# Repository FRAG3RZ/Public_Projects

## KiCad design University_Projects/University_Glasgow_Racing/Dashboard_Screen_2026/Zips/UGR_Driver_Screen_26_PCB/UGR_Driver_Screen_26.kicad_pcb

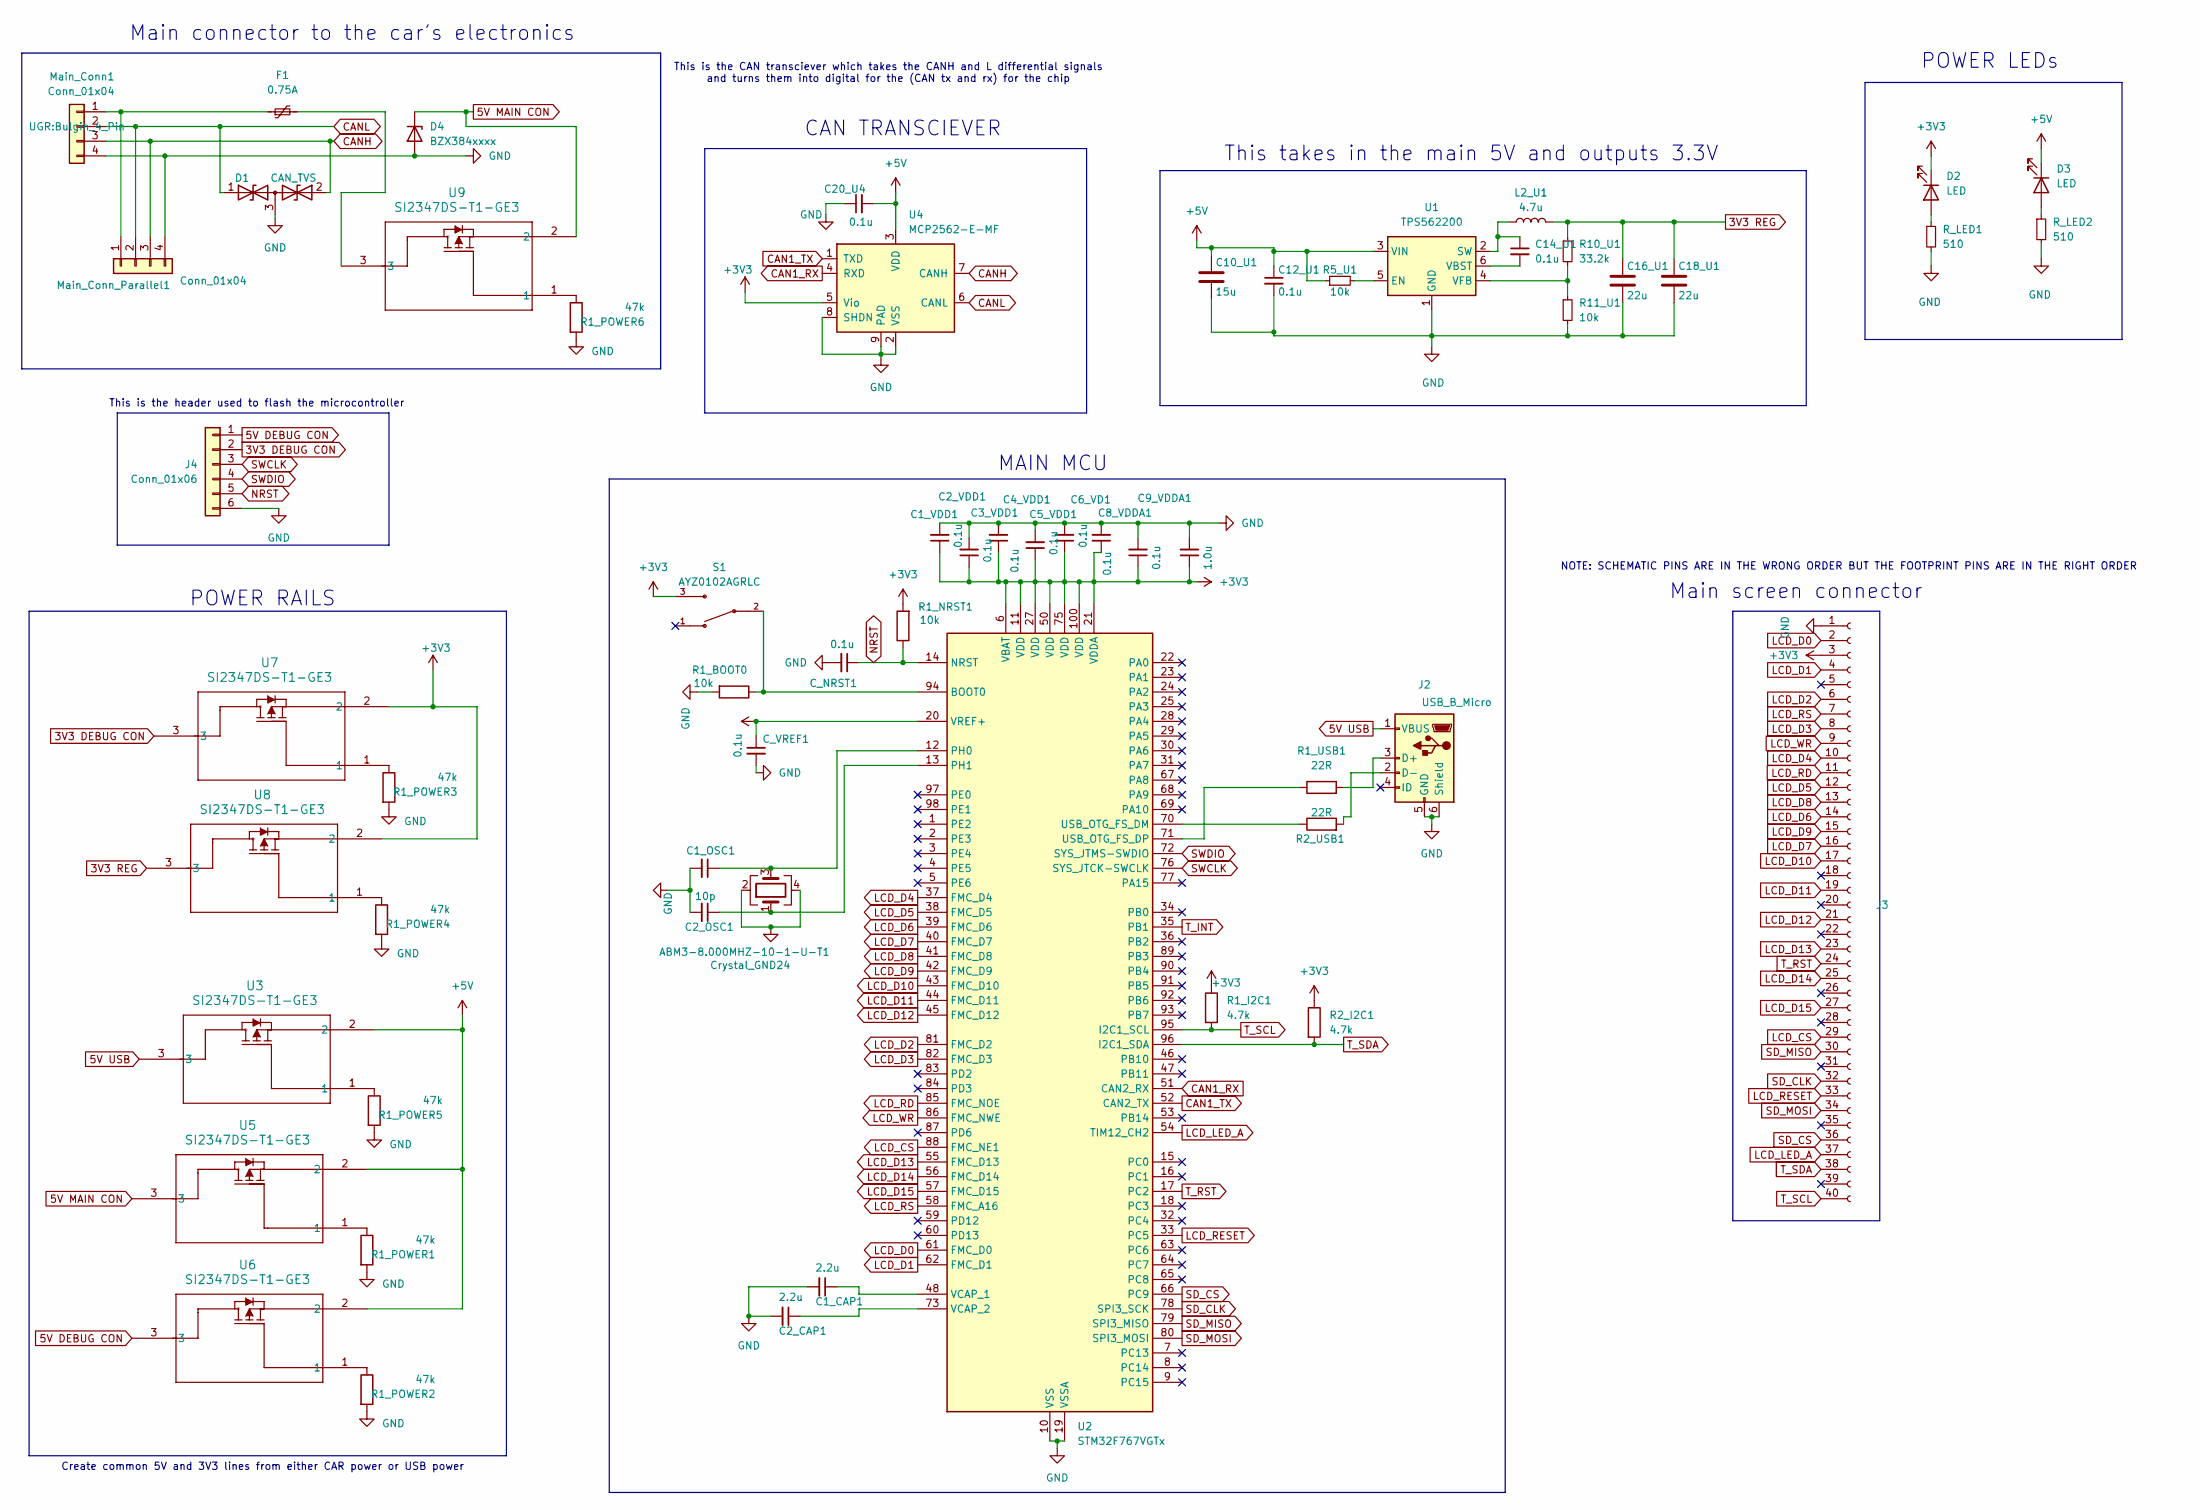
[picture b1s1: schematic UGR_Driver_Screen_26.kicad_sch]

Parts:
ABM3-8.000MHZ-10-1-U-T1: Crystal_GND24; Crystal_SMD_Abracon_ABM3B-4Pin_5.0x3.2mm
C1_CAP1, C2_CAP1: 2.2u; C_0603_1608Metric_Pad1.08x0.95mm_HandSolder
C1_OSC1, C2_OSC1: 10p; C_0603_1608Metric_Pad1.08x0.95mm_HandSolder
C1_VDD1, C2_VDD1, C3_VDD1, C4_VDD1, C5_VDD1, C6_VD1, C8_VDDA1, C12_U1, C14_U1, C20_U4: 0.1u; C_0603_1608Metric_Pad1.08x0.95mm_HandSolder
C9_VDDA1: 1.0u; C_0603_1608Metric_Pad1.08x0.95mm_HandSolder
C10_U1: 15u; C_1210_3225Metric_Pad1.33x2.70mm_HandSolder
C16_U1, C18_U1: 22u; C_1210_3225Metric_Pad1.33x2.70mm_HandSolder
C_NRST1: 0.1u; C_0603_1608Metric_Pad1.08x0.95mm_HandSolder
C_VREF1: 0.1u; C_0603_1608Metric_Pad1.08x0.95mm_HandSolder
D1: CAN_TVS; SOT-23; Manufacturer Part No. SZNUP2105L
D2, D3: LED; PinHeader_1x02_P2.54mm_Vertical
D4: BZX384xxxx; D_SOD-323
F1: 0.75A; Fuse_1812_4532Metric_Pad1.30x3.40mm_HandSolder; Manufacturer Part No. 1206L075/16WR
J2: USB_B_Micro; USB_Micro-B_Wuerth_629105150521
J3: Conn_02x20_Socket; PinSocket_2x20_P2.54mm_Vertical
J4: Conn_01x06; PinHeader_1x06_P2.54mm_Vertical
L2_U1: 4.7u; L_1206_3216Metric_Pad1.42x1.75mm_HandSolder
Main_Conn1: Conn_01x04; Bulgin_4_Pin
Main_Conn_Parallel1: Conn_01x04; PinHeader_1x04_P2.54mm_Vertical
R1_BOOT0, R1_NRST1, R5_U1, R11_U1: 10k; R_0603_1608Metric_Pad0.98x0.95mm_HandSolder
R1_I2C1, R2_I2C1: 4.7k; R_0603_1608Metric_Pad0.98x0.95mm_HandSolder
R1_POWER1, R1_POWER2, R1_POWER3, R1_POWER4, R1_POWER5, R1_POWER6: 47k; R_0603_1608Metric_Pad0.98x0.95mm_HandSolder
R1_USB1, R2_USB1: 22R; R_0603_1608Metric_Pad0.98x0.95mm_HandSolder
R10_U1: 33.2k; R_0603_1608Metric_Pad0.98x0.95mm_HandSolder
R_LED1, R_LED2: 510; R_0603_1608Metric_Pad0.98x0.95mm_HandSolder
S1: AYZ0102AGRLC; SW_AYZ0102AGRLC
U1: TPS562200; SOT-23-6
U2: STM32F767VGTx; LQFP-100_14x14mm_P0.5mm
U3, U5, U6, U7, U8, U9: SI2347DS-T1-GE3; SOT_7DS-T1-GE3_VIS
U4: MCP2562-E-MF; SOIC-8_3.9x4.9mm_P1.27mm

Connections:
3V3 DEBUG CON: J4.2, U7.3
3V3 REG: C16_U1.1, C18_U1.1, L2_U1.2, R10_U1.1, U8.3
5V DEBUG CON: J4.1, U6.3
5V MAIN CON: D4.1 (K), U5.3, U9.2
5V USB: J2.1 (VBUS), U3.3
+3V3: C1_VDD1.1, C2_VDD1.1, C3_VDD1.1, C4_VDD1.1, C5_VDD1.1, C6_VD1.1, C8_VDDA1.1, C9_VDDA1.1, C_VREF1.1, D2.1 (K), J3.3, R1_I2C1.1, R1_NRST1.2, R2_I2C1.1, S1.3, U2.6 (VBAT), U2.11 (VDD), U2.20 (VREF+), U2.21 (VDDA), U2.27 (VDD), U2.50 (VDD), U2.75 (VDD), U2.100 (VDD), U4.5 (Vio), U7.2, U8.2; also elsewhere on the board
+5V: C10_U1.1, C12_U1.1, C20_U4.2, D3.1 (K), R5_U1.1, U1.3 (VIN), U3.2, U4.3 (VDD), U5.2, U6.2; also elsewhere on the board
CAN1_RX: U2.51 (CAN2_RX), U4.4 (RXD)
CAN1_TX: U2.52 (CAN2_TX), U4.1 (TXD)
CANH: D1.2 (A2), Main_Conn1.3, Main_Conn_Parallel1.3, U4.7 (CANH)
CANL: D1.1 (A1), Main_Conn1.2, Main_Conn_Parallel1.2, U4.6 (CANL)
GND: ABM3-8.000MHZ-10-1-U-T1.2, ABM3-8.000MHZ-10-1-U-T1.4, C1_CAP1.2, C1_OSC1.2, C1_VDD1.2, C2_CAP1.2, C2_OSC1.2, C2_VDD1.2, C3_VDD1.2, C4_VDD1.2, C5_VDD1.2, C6_VD1.2, C8_VDDA1.2, C9_VDDA1.2, C10_U1.2, C12_U1.2, C16_U1.2, C18_U1.2, C20_U4.1, C_NRST1.2, C_VREF1.2, D1.3 (common), D4.2 (A), J2.5 (GND), J2.6 (Shield), J3.1, J4.6, Main_Conn1.4, Main_Conn_Parallel1.4, R1_BOOT0.2, R1_POWER1.2, R1_POWER2.2, R1_POWER3.2, R1_POWER4.2, R1_POWER5.2, R1_POWER6.2, R11_U1.2, R_LED1.2, R_LED2.2, U1.1 (GND), U2.10 (VSS), U2.19 (VSSA), U2.26 (VSS), U2.49 (VSS), U2.74 (VSS), U2.99 (VSS), U4.2 (VSS), U4.8 (SHDN), U4.9 (PAD)
LCD_CS: J3.29, U2.88 (FMC_NE1)
LCD_D0: J3.2, U2.61 (FMC_D0)
LCD_D1: J3.4, U2.62 (FMC_D1)
LCD_D2: J3.6, U2.81 (FMC_D2)
LCD_D3: J3.8, U2.82 (FMC_D3)
LCD_D4: J3.10, U2.37 (FMC_D4)
LCD_D5: J3.12, U2.38 (FMC_D5)
LCD_D6: J3.14, U2.39 (FMC_D6)
LCD_D7: J3.16, U2.40 (FMC_D7)
LCD_D8: J3.13, U2.41 (FMC_D8)
LCD_D9: J3.15, U2.42 (FMC_D9)
LCD_D10: J3.17, U2.43 (FMC_D10)
LCD_D11: J3.19, U2.44 (FMC_D11)
LCD_D12: J3.21, U2.45 (FMC_D12)
LCD_D13: J3.23, U2.55 (FMC_D13)
LCD_D14: J3.25, U2.56 (FMC_D14)
LCD_D15: J3.27, U2.57 (FMC_D15)
LCD_LED_A: J3.37, U2.54 (TIM12_CH2)
LCD_RD: J3.11, U2.85 (FMC_NOE)
LCD_RESET: J3.33, U2.33 (PC5)
LCD_RS: J3.7, U2.58 (FMC_A16)
LCD_WR: J3.9, U2.86 (FMC_NWE)
NRST: C_NRST1.1, J4.5, R1_NRST1.1, U2.14 (NRST)
unnamed 35: D2.2 (A), R_LED1.1; also elsewhere on the board
unnamed 36: D3.2 (A), R_LED2.1; also elsewhere on the board
unnamed: F1.2, U9.3
unnamed: J2.3 (D+), R1_USB1.2
unnamed: J2.2 (D-), R2_USB1.2
unnamed: F1.1, Main_Conn1.1, Main_Conn_Parallel1.1
unnamed: R1_POWER1.1, U5.1
unnamed: R1_POWER2.1, U6.1
unnamed: R1_POWER3.1, U7.1
unnamed: R1_POWER4.1, U8.1
unnamed: R1_POWER5.1, U3.1
unnamed: R1_POWER6.1, U9.1
unnamed: R5_U1.2, U1.5 (EN)
unnamed: C14_U1.1, L2_U1.1, U1.2 (SW)
unnamed: C14_U1.2, U1.6 (VBST)
unnamed: R10_U1.2, R11_U1.1, U1.4 (VFB)
unnamed: R1_BOOT0.1, S1.2, U2.94 (BOOT0)
unnamed: R2_USB1.1, U2.70 (USB_OTG_FS_DM)
unnamed: R1_USB1.1, U2.71 (USB_OTG_FS_DP)
unnamed: ABM3-8.000MHZ-10-1-U-T1.3, C1_OSC1.1, U2.12 (PH0)
unnamed: ABM3-8.000MHZ-10-1-U-T1.1, C2_OSC1.1, U2.13 (PH1)
unnamed: C1_CAP1.1, U2.48 (VCAP_1)
unnamed: C2_CAP1.1, U2.73 (VCAP_2)
SD_CLK: J3.32, U2.78 (SPI3_SCK)
SD_CS: J3.36, U2.66 (PC9)
SD_MISO: J3.30, U2.79 (SPI3_MISO)
SD_MOSI: J3.34, U2.80 (SPI3_MOSI)
SWCLK: J4.3, U2.76 (SYS_JTCK-SWCLK)
SWDIO: J4.4, U2.72 (SYS_JTMS-SWDIO)
T_INT: U2.35 (PB1)
T_RST: J3.24, U2.17 (PC2)
T_SCL: J3.40, R1_I2C1.2, U2.95 (I2C1_SCL)
T_SDA: J3.38, R2_I2C1.2, U2.96 (I2C1_SDA)

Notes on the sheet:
POWER RAILS
Create common 5V and 3V3 lines from either CAR power or USB power
Main screen connector
POWER LEDs
MAIN MCU
This takes in the main 5V and outputs 3.3V
Main connector to the car's electronics
CAN TRANSCIEVER
This is the CAN transciever which takes the CANH and L differential signals and turns them into digital for the (CAN tx and rx) for the chip
This is the header used to flash the microcontroller
NOTE: SCHEMATIC PINS ARE IN THE WRONG ORDER BUT THE FOOTPRINT PINS ARE IN THE RIGHT ORDER

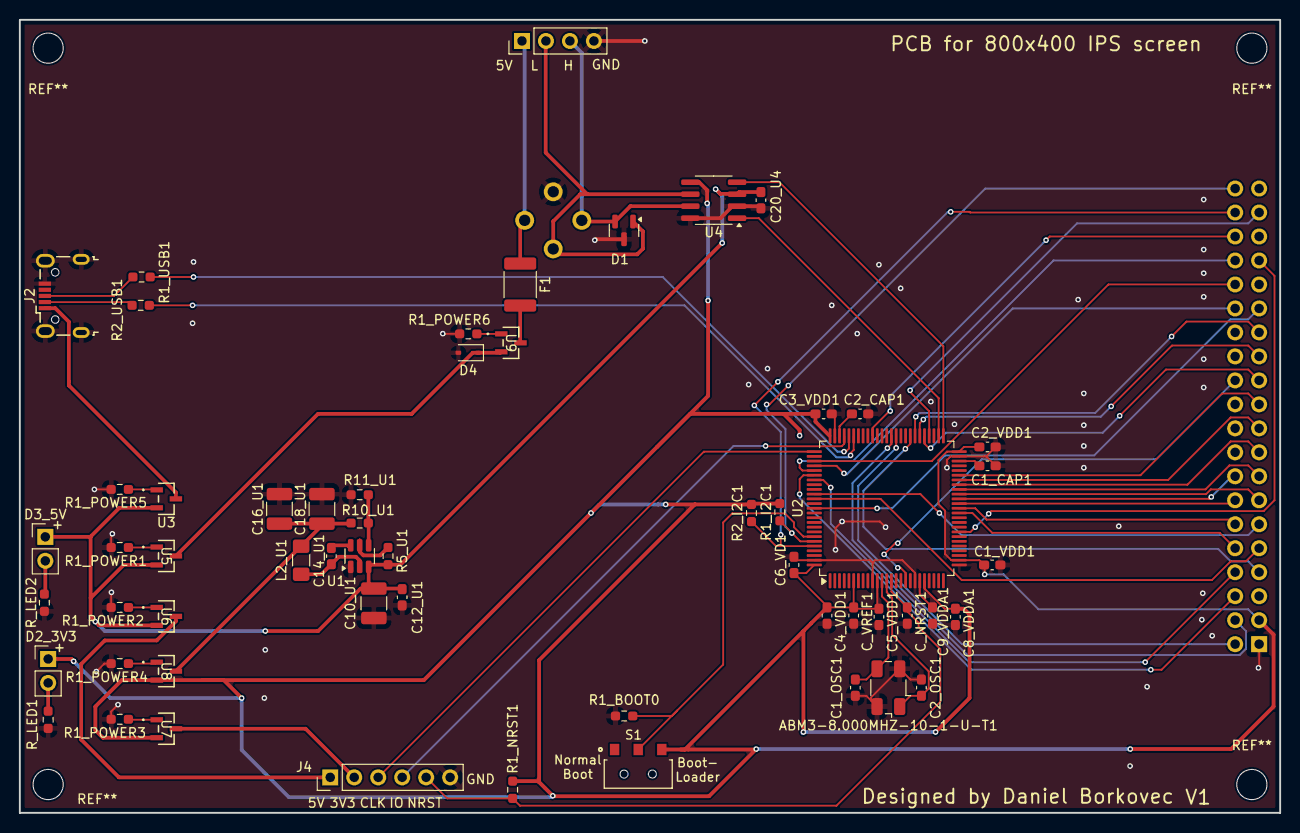
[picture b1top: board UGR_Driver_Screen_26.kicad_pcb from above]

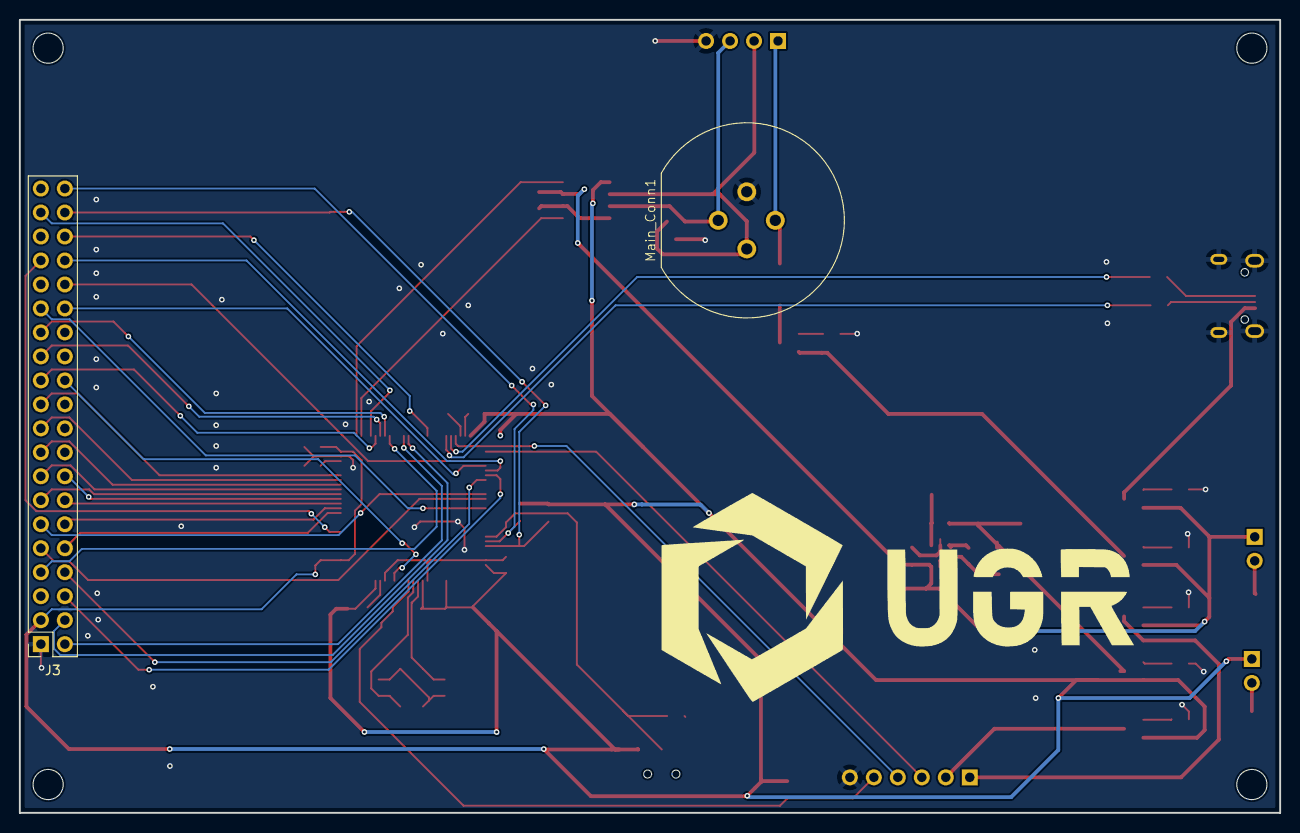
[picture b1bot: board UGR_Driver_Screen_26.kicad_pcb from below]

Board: 2 copper layers, 133.5 x 84.0 mm, 59 parts (2 on the bottom side), 67 nets.

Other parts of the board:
D2_3V3, D3_5V: LED; PinHeader_1x02_P2.54mm_Vertical

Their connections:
+3V3: D2_3V3.1 (K); also elsewhere on the board
+5V: D3_5V.1 (K); also elsewhere on the board
unnamed 35: D2_3V3.2 (A); also elsewhere on the board
unnamed 36: D3_5V.2 (A); also elsewhere on the board

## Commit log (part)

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2026-06-16 Rename
2026-06-16 Dashboard Improvements
